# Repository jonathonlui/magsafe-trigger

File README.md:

## MagSafe Trigger

Use a MagSafe 2 Power Adapter to power other devices.

Based on info from [Macbook charger teardown from Ken Shirriff's blog](http://www.righto.com/2015/11/macbook-charger-teardown-surprising.html) (see section **Operation of the charger** and [footnote 15](http://www.righto.com/2015/11/macbook-charger-teardown-surprising.html#ref15) and [16](http://www.righto.com/2015/11/macbook-charger-teardown-surprising.html#ref16))

### Schematic

### BOM

- MagSafe 2 "female" connector/jack
  - Harvested from faulty port
  - Is also available on aliexpress/ebay usually on a small PCB with a 
- IRF3708 MOSFET TO-220
  - It's what I have on hand. It's considered obsolete but can be purchased from Chinese sellers (via aliexpress, ebay) for $3 shipped for 10 pieces.
- 0.5 Watt 10V Zener diode DO-35
  - It's also what I have on hand.
- 39K Ohm resistor 1206
  - Use to apply low-voltage load to trigger
  - Can probably ok to use 33K-47K Ohm
- 10K Ohm resistor 1206
  - To pull down MOSFET gate to keep it off until full voltage
- LED 1206 (optional)
- 1K2 Ohm resistor 1206 (optional)

MagSafe power adapter output a low voltage until it detects about 39K Ohm load. The low voltage depends on the model and version of the MagSafe adapter and will be between 0.6V to 6V.

The Zener diode blocks current to the MOSFET gate until the voltage is above the Zener’s reverse breakdown voltage. Using a 10V Zener diode keeps the output off until the MagSafe adapter switches to full voltage.

Full voltage is 14.5V to 20V depending on MagSafe model. With the 10V Zener inline the gate voltage when full voltage is between 4.5V to 10V which is enough to fully turn on the MOSFET.

Without the MOSFET blocking current though the OUTPUT,  any load on the OUTPUT will prevent the MagSafe power adapter from switch from low voltage to high voltage..

ID_LED pin is connected to a chip inside the the male connector. It is normally used by Apple laptops to read the type and id/serial number of power supply and to turn on and off the LEDS. It does not need to be used to trigger the full voltage

### PCB Layout

MagSafe jack footprint is based on manual measurements and probably needs tweaking for proper fit. 

### PCB rendering

### Assembly

### Powered

Plugging in a 45 W MagSafe 2 Power Adapter shows 15 V open circuit.

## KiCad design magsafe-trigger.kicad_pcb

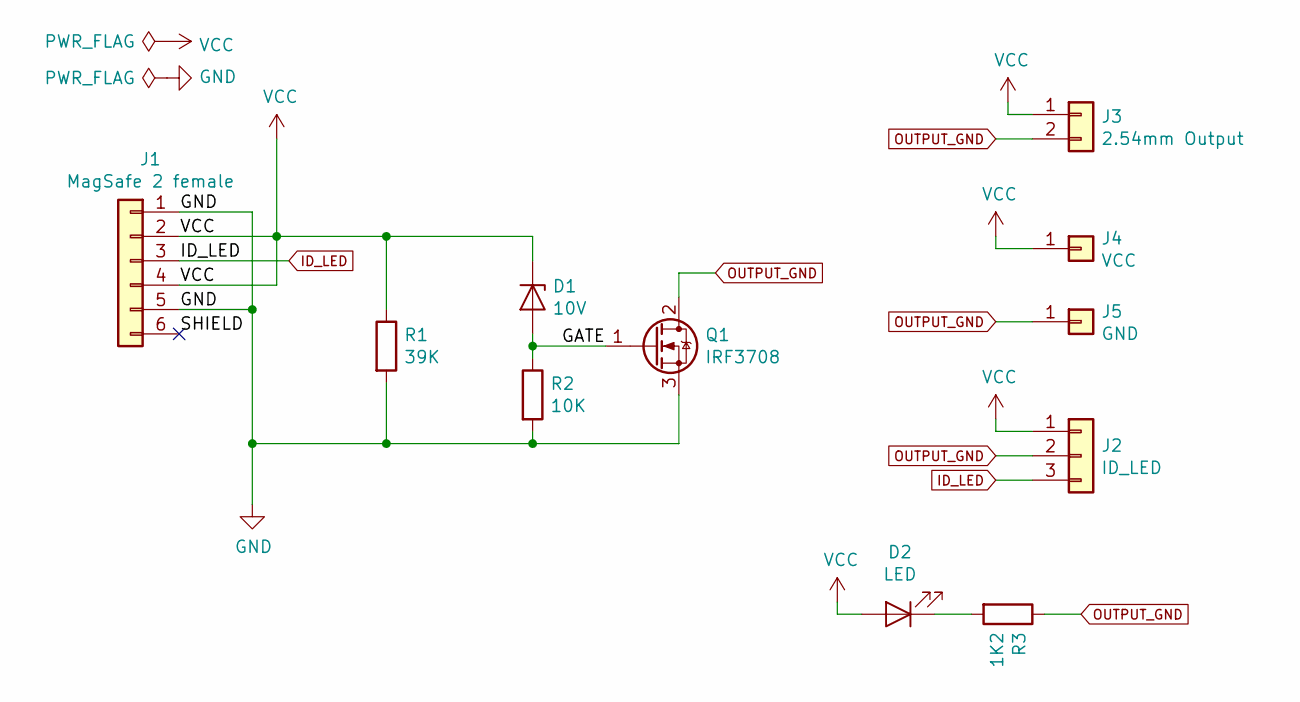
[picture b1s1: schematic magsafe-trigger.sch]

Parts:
D1: 10V; D_DO-35_SOD27_P7.62mm_Horizontal
D2: LED; LED_1206_3216Metric_Pad1.42x1.75mm_HandSolder
J1: MagSafe 2 female; MagSafe_2_Female
J2: ID_LED; PinSocket_1x03_P2.54mm_Vertical
J3: 2.54mm Output; PinHeader_1x02_P2.54mm_Vertical
J4: VCC; TestPoint_THTPad_4.0x4.0mm_Drill2.0mm
J5: GND; TestPoint_THTPad_4.0x4.0mm_Drill2.0mm
Q1: IRF3708; TO-220-3_Horizontal_TabDown
R1: 39K; R_1206_3216Metric_Pad1.42x1.75mm_HandSolder
R2: 10K; R_1206_3216Metric_Pad1.42x1.75mm_HandSolder
R3: 1K2; R_1206_3216Metric_Pad1.42x1.75mm_HandSolder

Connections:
/GATE: D1.2 (A), Q1.1 (G), R2.1
/SHIELD: J1.6; also elsewhere on the board
GND: J1.1, J1.5, Q1.3 (S), R1.2, R2.2; also elsewhere on the board
ID_LED: J1.3, J2.3; also elsewhere on the board
unnamed: D2.1 (K), R3.2
OUTPUT_GND: J2.2, J3.2, J5.1, Q1.2 (D), R3.1
VCC: D1.1 (K), D2.2 (A), J1.2, J1.4, J2.1, J3.1, J4.1, R1.1; also elsewhere on the board

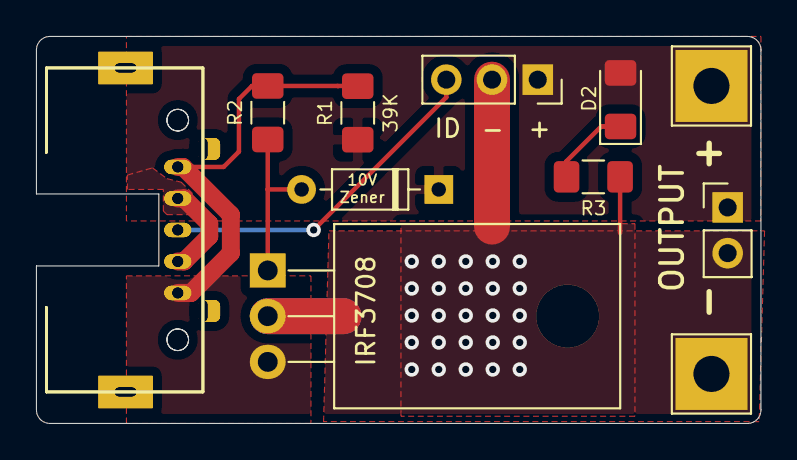
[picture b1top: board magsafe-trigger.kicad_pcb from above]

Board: 2 copper layers, 40.2 x 21.5 mm, 12 parts (0 on the bottom side), 7 nets.

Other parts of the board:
J1#2: MagSafe 2 female; MagSafe_2_Female

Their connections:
/SHIELD: J1#2.6; also elsewhere on the board
GND: J1#2.1, J1#2.5; also elsewhere on the board
ID_LED: J1#2.3; also elsewhere on the board
VCC: J1#2.2, J1#2.4; also elsewhere on the board

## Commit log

2020-01-16 Schematic and PCB design
2020-02-05 Update PCB connect MOSFET tab to output gnd
    - Add more labels
    - Remove back exposed copper
2020-05-18 Add assembled images
